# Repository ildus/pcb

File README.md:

My PCBs
-------

I keep my PCBs here. Feel free to use them.
For now i have:

* Amplifier based on TDA7386, adapted to use with Toyota OEM car stereo connector

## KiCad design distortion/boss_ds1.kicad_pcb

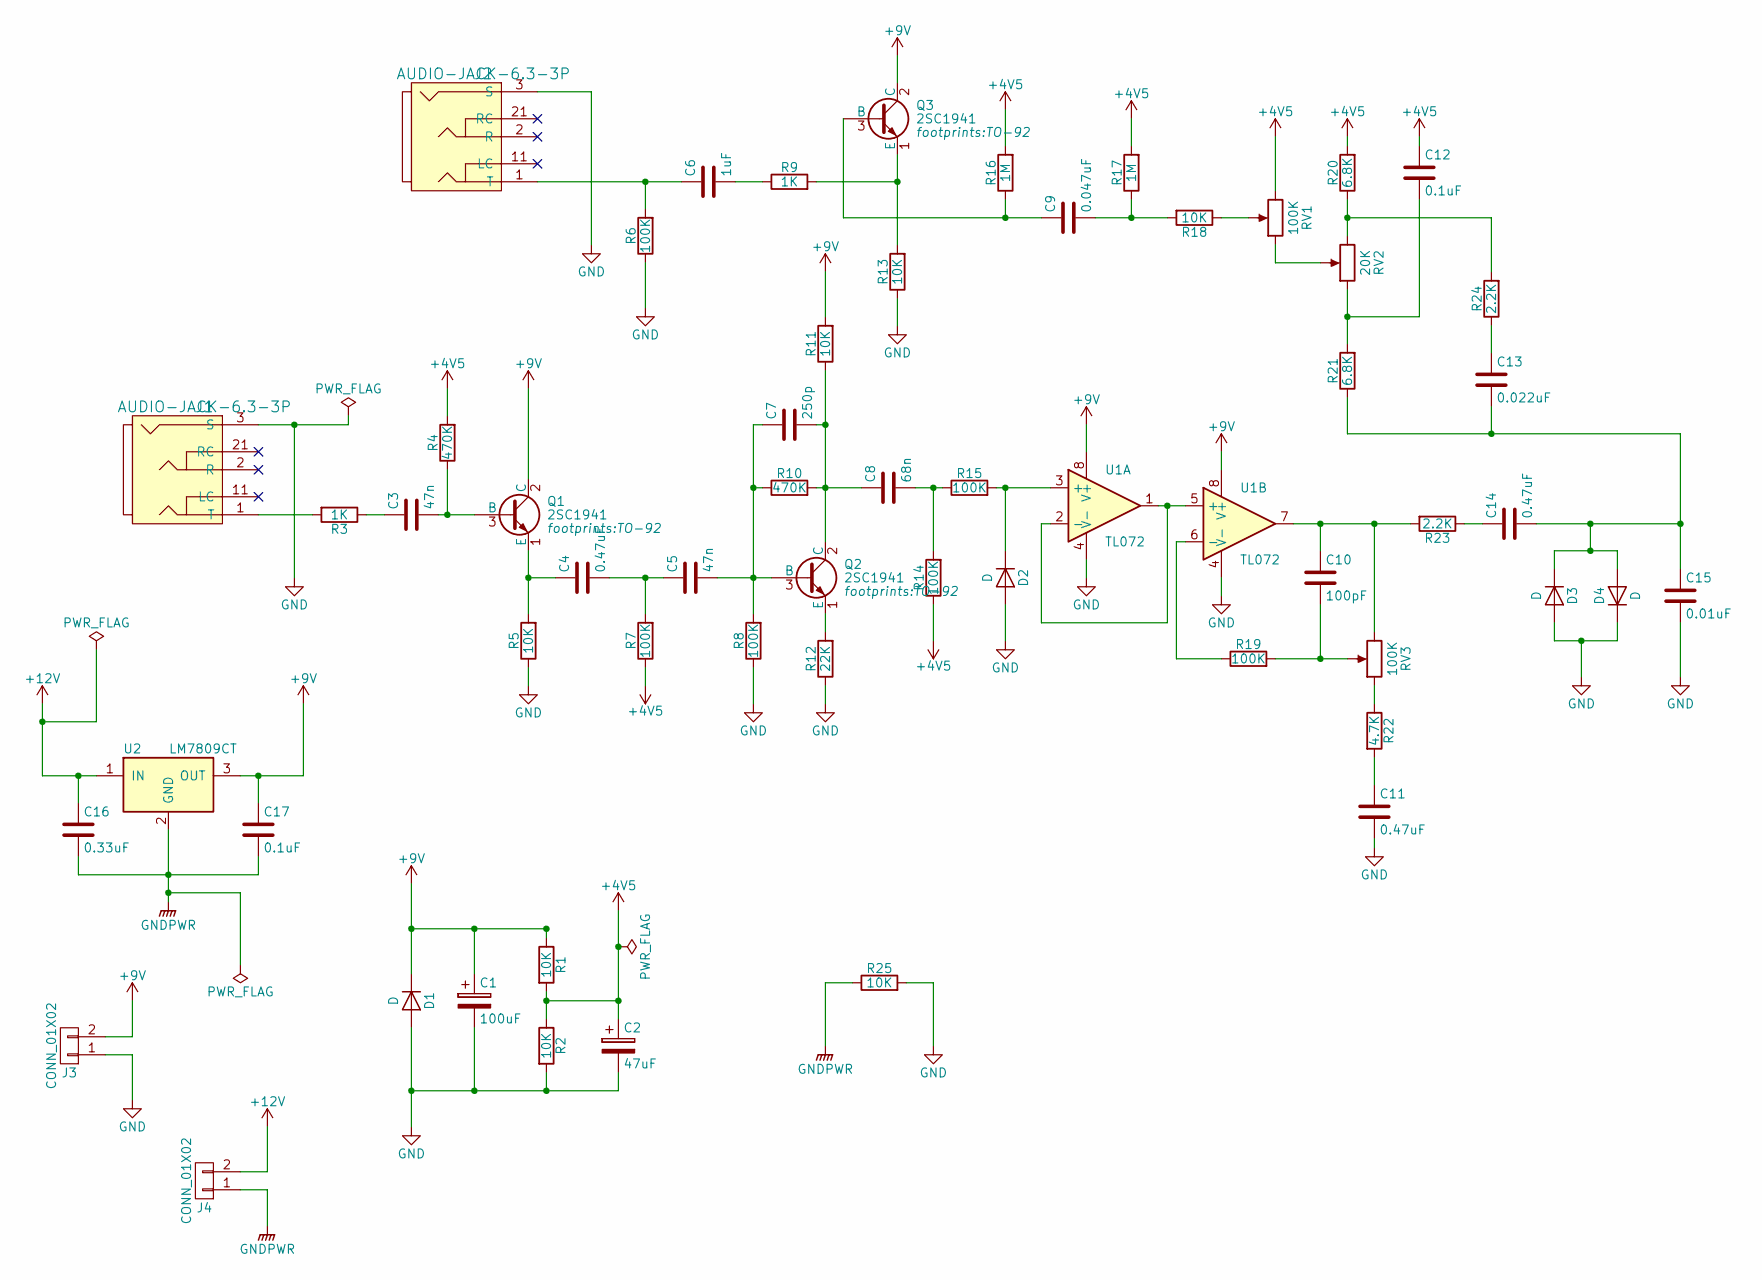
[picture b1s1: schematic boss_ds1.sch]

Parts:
C1: 100uF; CP_Elec_4x5.8
C2: 47uF; CP_Elec_3x5.3
C3, C5: 47n; C_0805_HandSoldering
C4, C11, C14: 0.47uF; C_0805_HandSoldering
C6: 1uF; C_0805_HandSoldering
C7: 250p; C_0805_HandSoldering
C8: 68n; C_0805_HandSoldering
C9: 0.047uF; C_0805_HandSoldering
C10: 100pF; C_0805_HandSoldering
C12, C17: 0.1uF; C_0805_HandSoldering
C13: 0.022uF; C_0805_HandSoldering
C15: 0.01uF; C_0805_HandSoldering
C16: 0.33uF; C_0805_HandSoldering
D1, D2: D; D_DO-35_SOD27_P7.62mm_Horizontal
D3, D4: D; D_SOD-123
J1, J2: AUDIO-JACK-6.3-3P; Jack6P
J3, J4: CONN_01X02; PINHEAD1-2
Q1, Q2, Q3: 2SC1941; TO-92
R1, R2, R5, R11, R13, R18, R25: 10K; R_0805_HandSoldering
R3, R9: 1K; R_0805_HandSoldering
R4, R10: 470K; R_Axial_DIN0207_L6.3mm_D2.5mm_P10.16mm_Horizontal
R6, R7, R8, R14, R15, R19: 100K; R_1206_HandSoldering
R12: 22K; R_1206_HandSoldering
R16, R17: 1M; R_Axial_DIN0207_L6.3mm_D2.5mm_P10.16mm_Horizontal
R20, R21: 6.8K; R_0805_HandSoldering
R22: 4.7K; R_0805_HandSoldering
R23, R24: 2.2K; R_0805_HandSoldering
RV1, RV3: 100K; R0904N-SONG-HUEI
RV2: 20K; R0904N-SONG-HUEI
U1: TL072; SO-8
U2: LM7809CT; TO-220_Vertical

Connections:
+4V5: C2.1, C12.1, R1.2, R2.1, R4.2, R7.1, R14.1, R16.2, R17.2, R20.2, RV1.3
+9V: C1.1, C17.1, D1.1 (K), J3.2, Q1.2 (C), Q3.2 (C), R1.1, R11.2, U1.8 (V+), U2.3 (OUT)
+12V: C16.1, J4.2, U2.1 (IN)
GND: C1.2, C2.2, C11.2, C15.2, D1.2 (A), D2.2 (A), D3.2 (A), D4.1 (K), J1.3 (S), J2.3 (S), J3.1, R2.2, R5.1, R6.1, R8.1, R12.1, R13.1, R25.2, U1.4 (V-)
GNDPWR: C16.2, C17.2, J4.1, R25.1, U2.2 (GND)
unnamed: C3.1, R3.1
unnamed: C3.2, Q1.3 (B), R4.1
unnamed: C4.1, Q1.1 (E), R5.2
unnamed: C4.2, C5.1, R7.2
unnamed: C5.2, C7.1, Q2.3 (B), R8.2, R10.1
unnamed: C6.1, J2.1 (T), R6.2
unnamed: C6.2, R9.1
unnamed: C7.2, C8.1, Q2.2 (C), R10.2, R11.1
unnamed: C8.2, R14.2, R15.1
unnamed: C9.1, Q3.3 (B), R16.1
unnamed: C9.2, R17.1, R18.2
unnamed: C10.1, R23.2, RV3.3, U1.7
unnamed: C10.2, R19.2, RV3.2
unnamed: C11.1, R22.2
unnamed: C12.2, R21.2, RV2.1
unnamed: C13.1, R24.1
unnamed: C13.2, C14.2, C15.1, D3.1 (K), D4.2 (A), R21.1
unnamed: C14.1, R23.1
unnamed: D2.1 (K), R15.2, U1.3 (+)
unnamed: J1.1 (T), R3.2
unnamed: Q2.1 (E), R12.2
unnamed: Q3.1 (E), R9.2, R13.2
unnamed: R18.1, RV1.2
unnamed: R19.1, U1.6 (-)
unnamed: R20.1, R24.2, RV2.3
unnamed: R22.1, RV3.1
unnamed: RV1.1, RV2.2
unnamed: U1.1, U1.2 (-), U1.5 (+)

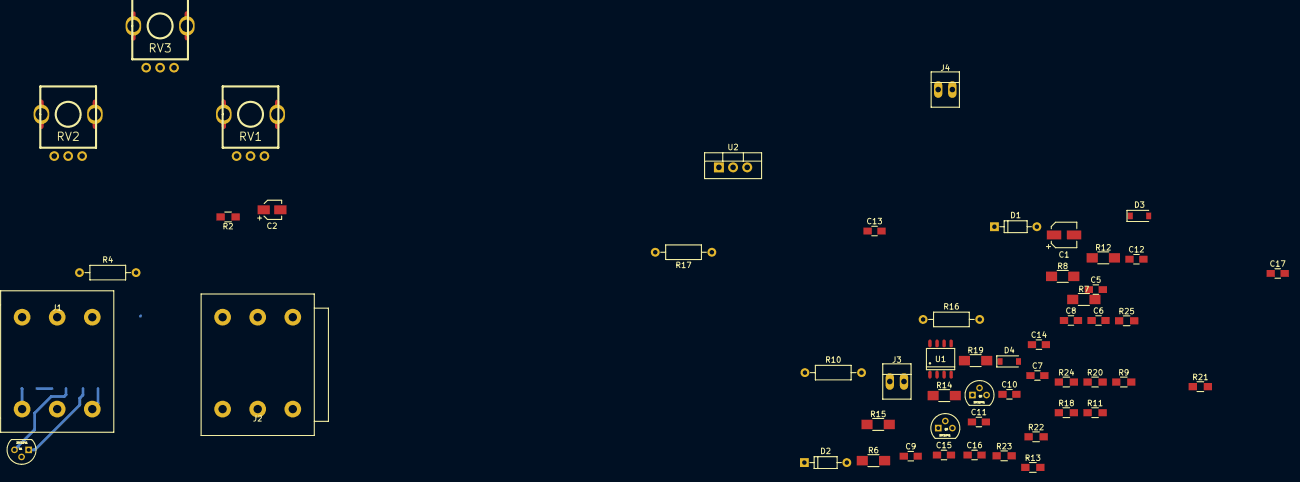
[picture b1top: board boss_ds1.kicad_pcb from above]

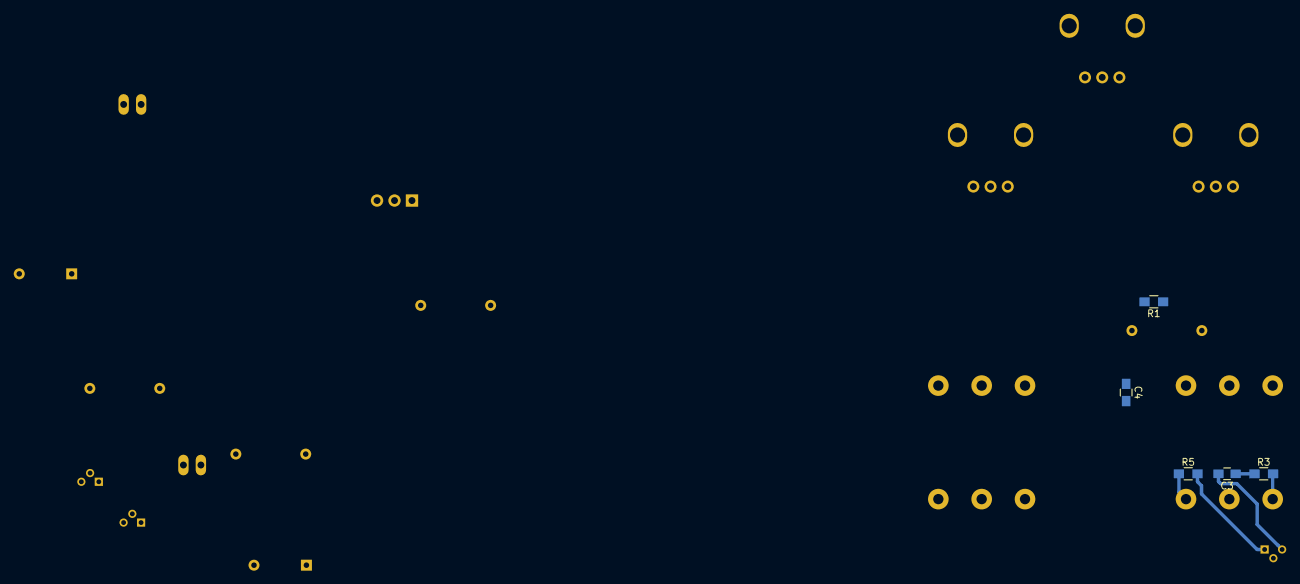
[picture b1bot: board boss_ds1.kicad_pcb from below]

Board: 2 copper layers, 58 parts (5 on the bottom side), 33 nets.

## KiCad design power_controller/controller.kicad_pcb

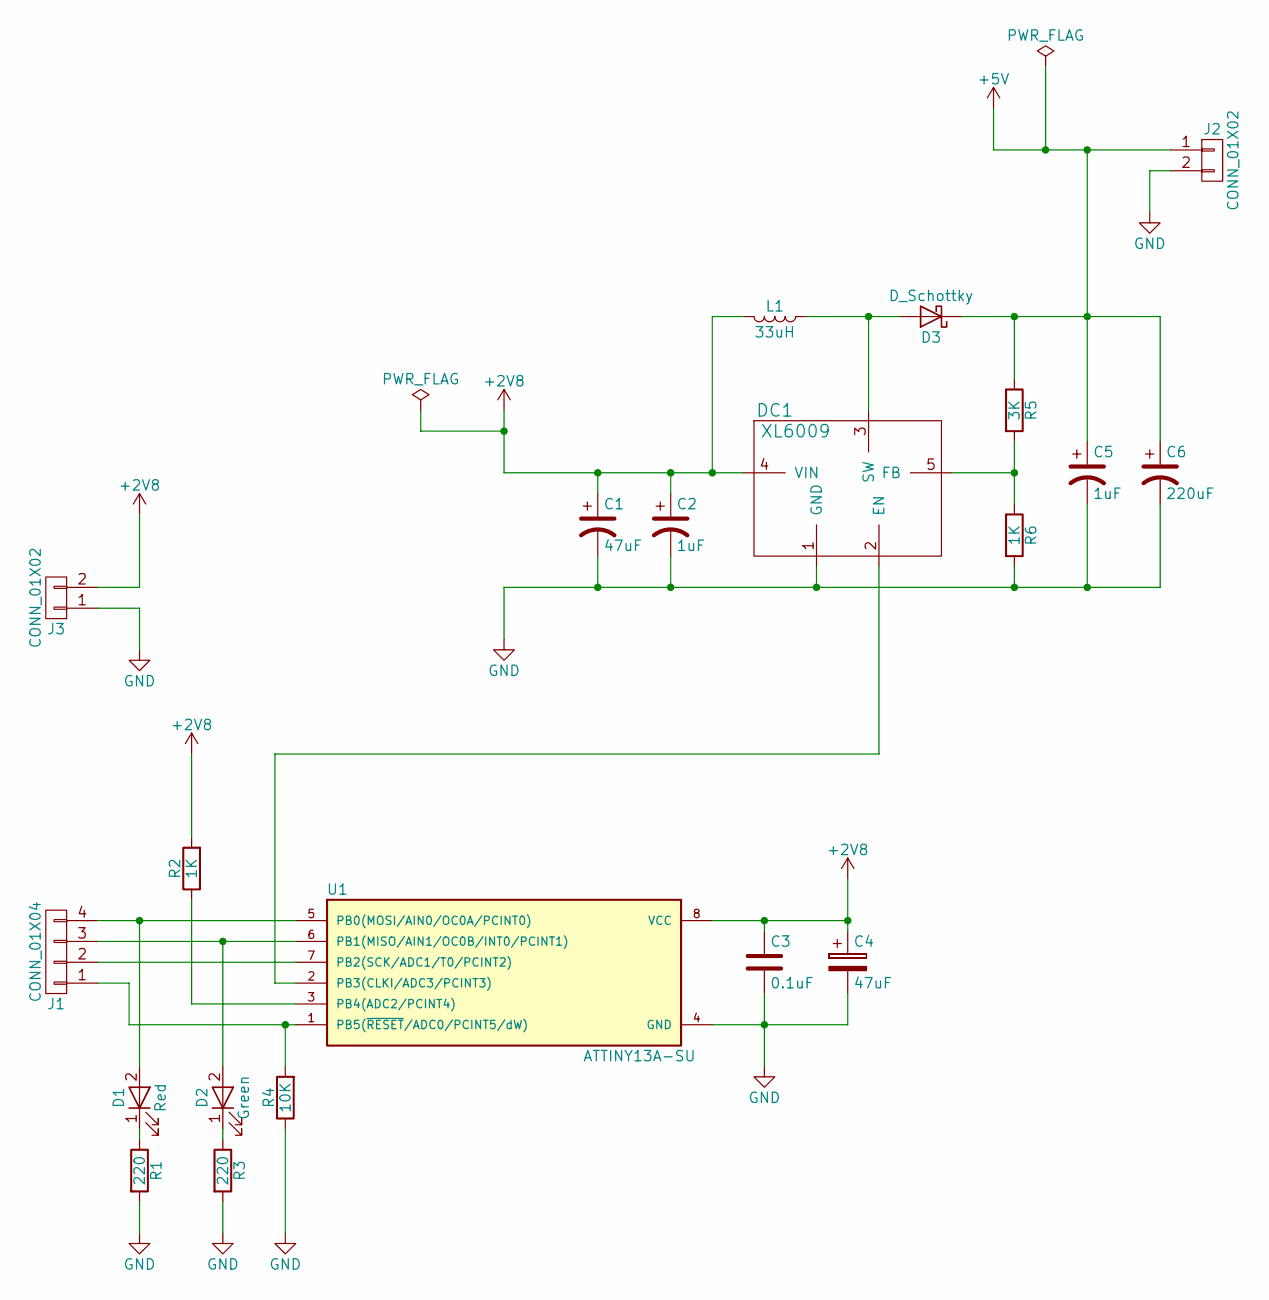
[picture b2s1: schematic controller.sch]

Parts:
C1, C4: 47uF; CP_Elec_5x5.3
C2, C5: 1uF; C_1210_HandSoldering
C3: 0.1uF; C_0805_HandSoldering
C6: 220uF; CP_Tantalum_Case-V_EIA-7343-20_Hand
D1: Red; LED_D1.8mm_W3.3mm_H2.4mm
D2: Green; LED_D1.8mm_W3.3mm_H2.4mm
D3: D_Schottky; D_DO-201_P12.70mm_Horizontal
DC1: XL6009; TO-263-5
J1: CONN_01X04; Grove_1x04
J2, J3: CONN_01X02; PINHEAD1-2
L1: 33uH; SELF-WE-PD-XXL
R1, R3: 220; R_1206_HandSoldering
R2, R6: 1K; R_1206_HandSoldering
R4: 10K; R_1206_HandSoldering
R5: 3K; R_1206_HandSoldering
U1: ATTINY13A-SU; SOIC-8_3.9x4.9mm_Pitch1.27mm

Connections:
+2V8: C1.1, C2.1, C3.1, C4.1, DC1.4 (VIN), J3.2, L1.2, R2.2, U1.8 (VCC)
+5V: C5.1, C6.1, D3.1 (K), J2.1, R5.1
GND: C1.2, C2.2, C3.2, C4.2, C5.2, C6.2, DC1.1 (GND), J2.2, J3.1, R1.2, R3.2, R4.1, R6.2, U1.4 (GND)
unnamed: D1.1 (K), R1.1
unnamed: D1.2 (A), J1.4, U1.5 (PB0(MOSI/AIN0/OC0A/PCINT0))
unnamed: D2.1 (K), R3.1
unnamed: D2.2 (A), J1.3, U1.6 (PB1(MISO/AIN1/OC0B/INT0/PCINT1))
unnamed: D3.2 (A), DC1.3 (SW), L1.1
unnamed: DC1.2 (EN), U1.2 (PB3(CLKI/ADC3/PCINT3))
unnamed: DC1.5 (FB), R5.2, R6.1
unnamed: J1.1, R4.2, U1.1 (PB5(~RESET~/ADC0/PCINT5/dW))
unnamed: J1.2, U1.7 (PB2(SCK/ADC1/T0/PCINT2))
unnamed: R2.1, U1.3 (PB4(ADC2/PCINT4))

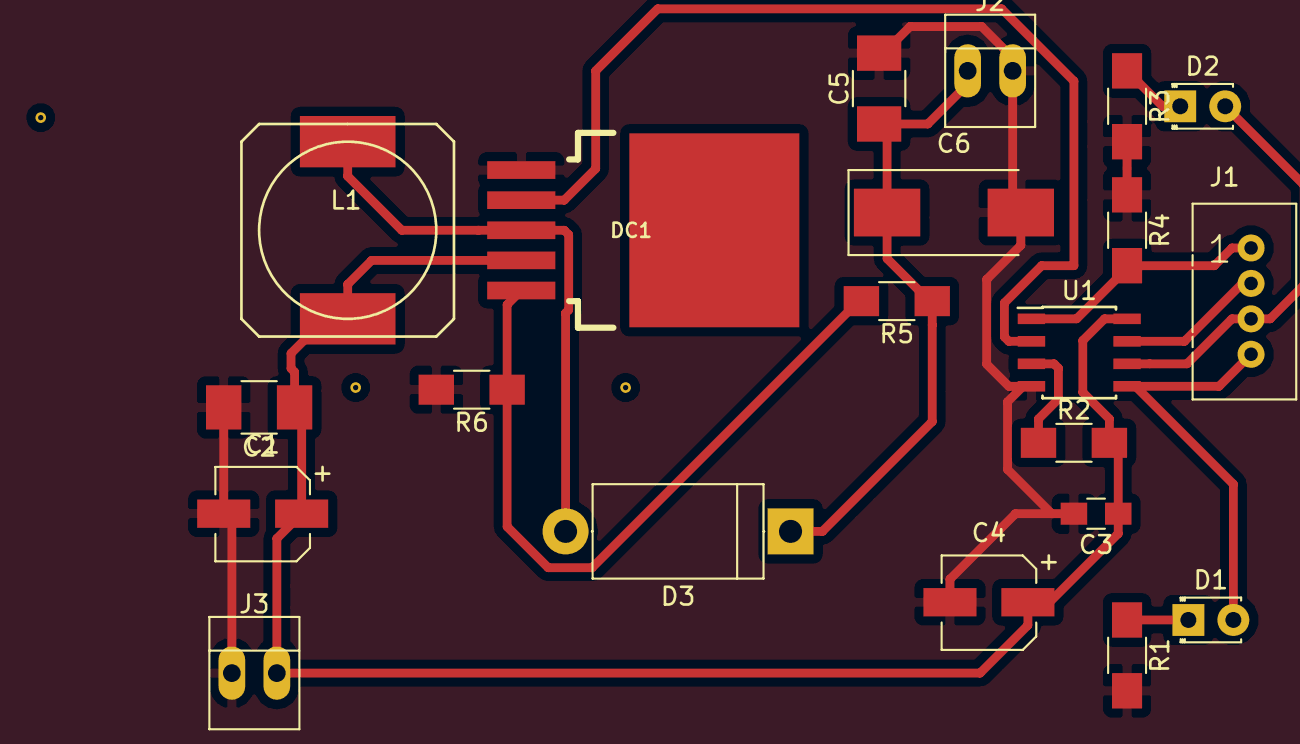
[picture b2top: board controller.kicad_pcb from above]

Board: 2 copper layers, 21 parts (0 on the bottom side), 13 nets.

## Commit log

2017-02-20 Initial
2017-04-16 Add distortion and power controller schematics
